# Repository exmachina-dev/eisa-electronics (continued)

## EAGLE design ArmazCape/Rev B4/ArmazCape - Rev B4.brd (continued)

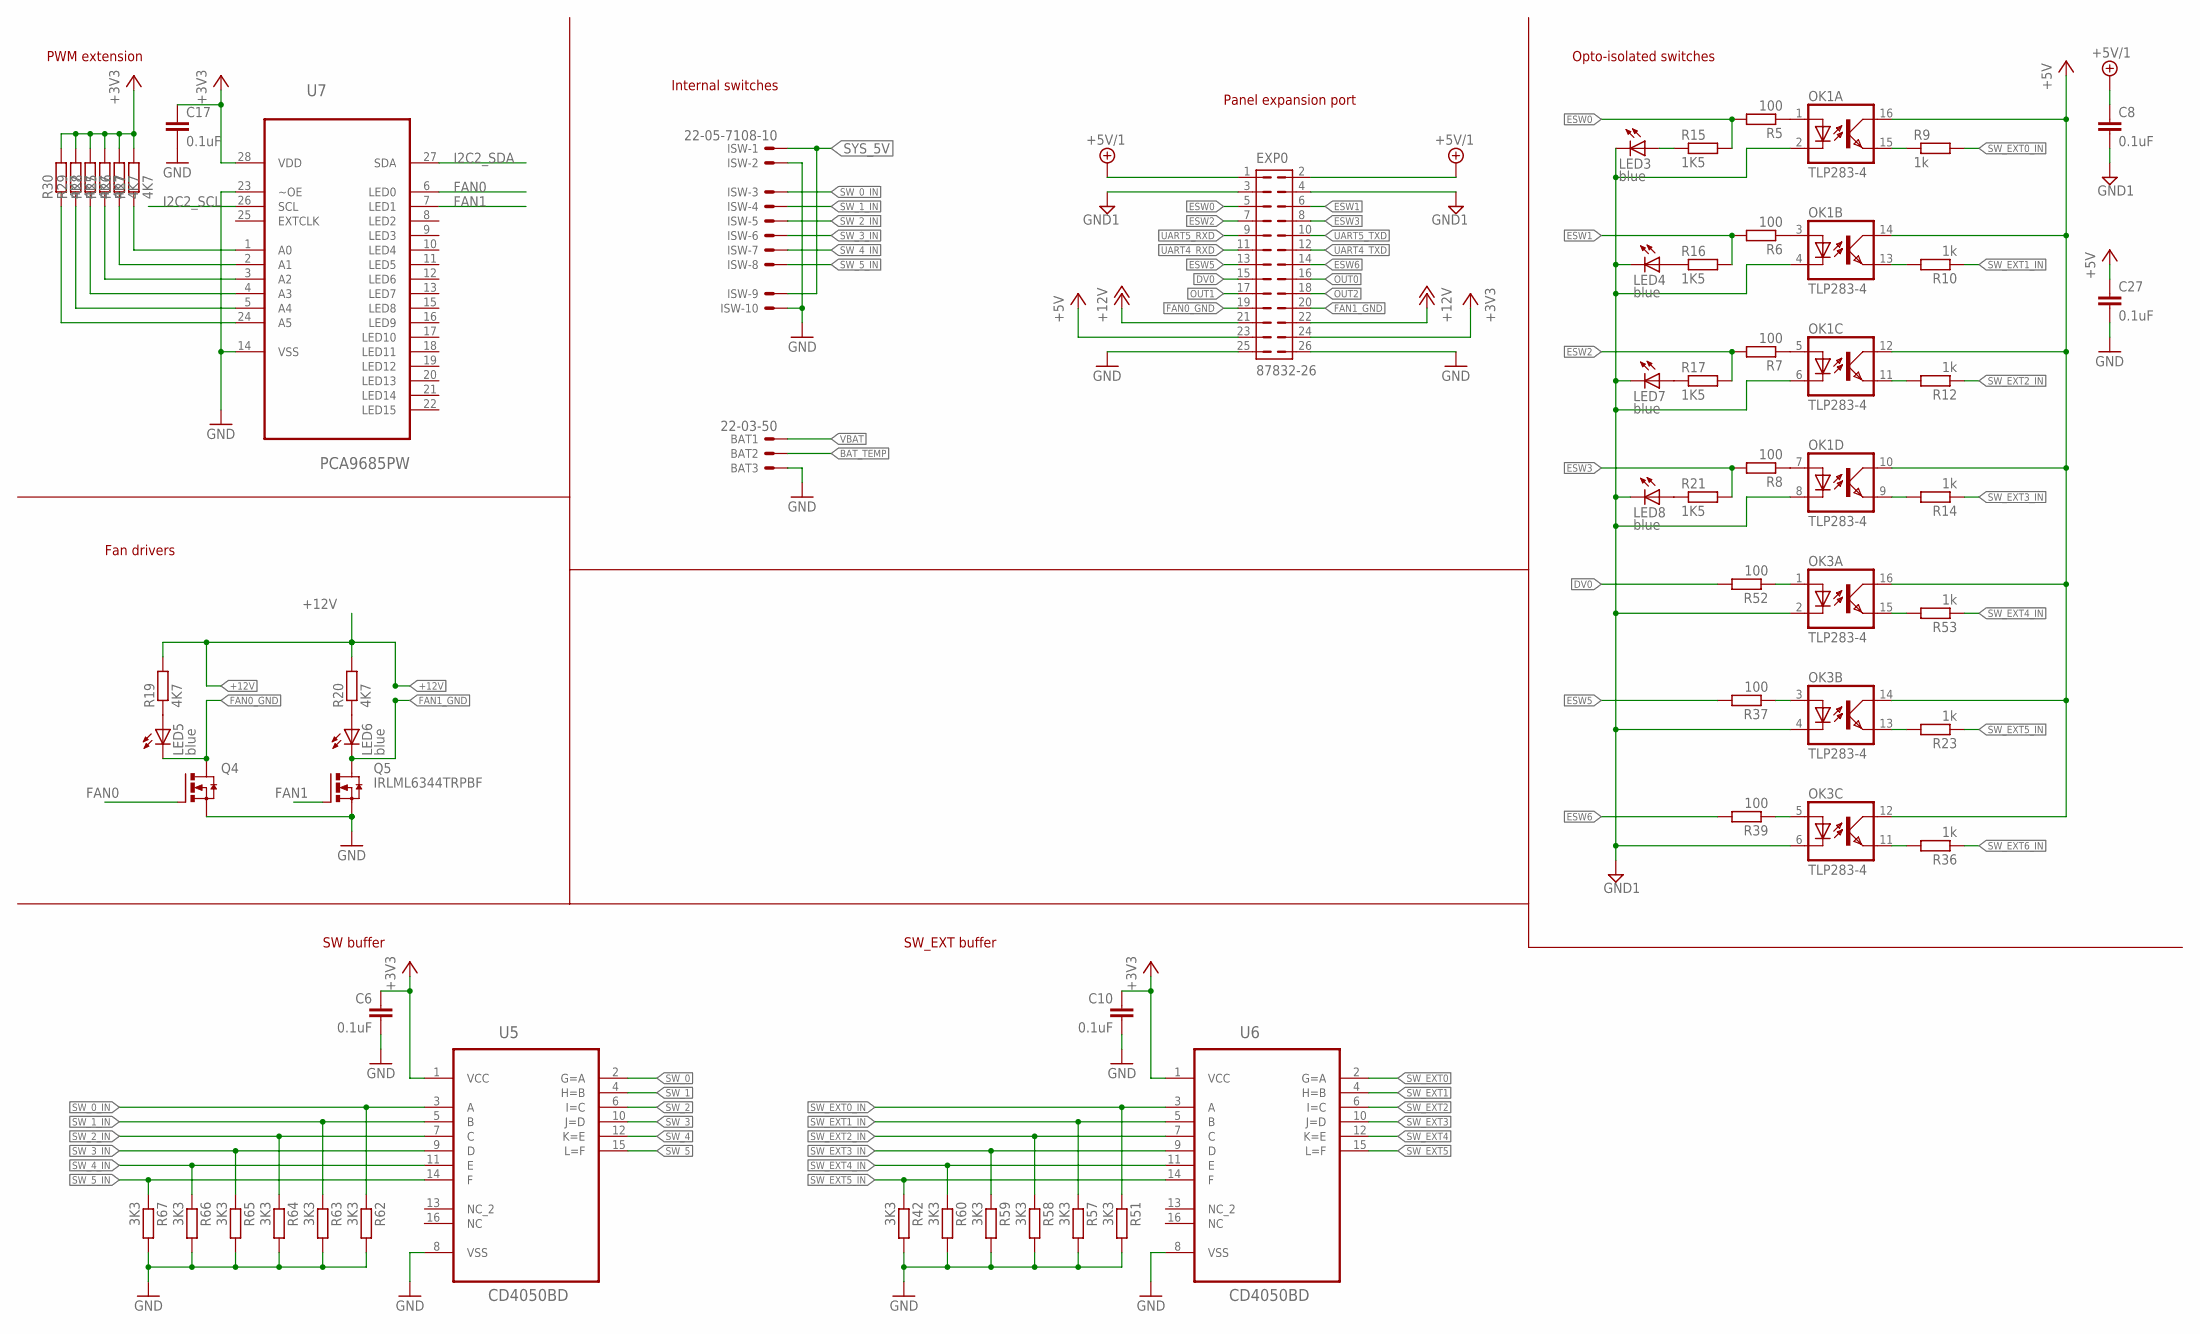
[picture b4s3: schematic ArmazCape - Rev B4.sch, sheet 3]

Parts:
BAT: 22-03-50; 5267-03A; MPN 22-03-5035
C6, C8, C10, C17, C27: 0.1uF; C0603; MPN GRM188R71H104KA93D
EXP0: 87832-26; MPN 87832-2620
ISW: 22-05-7108-10; 7395-10; MPN 22-05-7108
LED3, LED4, LED5, LED6, LED7, LED8: blue; CHIP-LED0603; MPN OVS-0603
OK1, OK3: TLP283-4; MINI-FLAT-16; MPN TCMT4100
Q4, Q5: IRLML6344TRPBF; SOT95P240X112-3N
R5, R6, R7, R8, R37, R39, R52: 100; R0603; MPN RC0603FR-07100RL
R9, R10, R12, R14, R23, R36, R53: 1k; R0603; MPN RC0603FR-071KL
R15, R16, R17, R21: 1K5; R0603; MPN RC0603FR-071K5L
R19, R20, R25, R26, R27, R28, R29, R30: 4K7; R0603; MPN RC0603FR-074K7L
R42, R51, R57, R58, R59, R60, R62, R63, R64, R65, R66, R67: 3K3; R0603; MPN RC0603FR-073K3L
U5, U6: CD4050BD; SOIC127P600X175-16N
U7: PCA9685PW; SOP65P640X110-28N

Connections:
+3V3: C6.1, C10.1, C17.1, EXP0.24, R25.2, R26.2, R27.2, R28.2, R29.2, R30.2, U5.1 (VCC), U6.1 (VCC), U7.28 (VDD); also elsewhere on the board
+5V: C27.1, EXP0.23, OK1.10 (COL), OK1.12 (COL), OK1.14 (COL), OK1.16 (COL), OK3.12 (COL), OK3.14 (COL), OK3.16 (COL); also elsewhere on the board
+5V/1: C8.1, EXP0.1, EXP0.2; also elsewhere on the board
+12V: EXP0.21, EXP0.22, R19.2, R20.2; also elsewhere on the board
BAT_TEMP: BAT.P2; also elsewhere on the board
DV0: EXP0.15, R52.2; also elsewhere on the board
ESW0: EXP0.5, R5.2, R15.2
ESW1: EXP0.6, R6.2, R16.2
ESW2: EXP0.7, R7.2, R17.2
ESW3: EXP0.8, R8.2, R21.2
ESW5: EXP0.13, R37.2
ESW6: EXP0.14, R39.2
FAN0: Q4.1 (G), U7.6 (LED0)
FAN0_GND: EXP0.19, LED5.C, Q4.3 (D)
FAN1: Q5.1 (G), U7.7 (LED1)
FAN1_GND: EXP0.20, LED6.C, Q5.3 (D)
GND: BAT.P3, C6.2, C10.2, C17.2, C27.2, EXP0.25, EXP0.26, ISW.2, ISW.10, Q4.2 (S), Q5.2 (S), R42.2, R51.2, R57.2, R58.2, R59.2, R60.2, R62.2, R63.2, R64.2, R65.2, R66.2, R67.2, U5.8 (VSS), U6.8 (VSS), U7.14 (VSS), U7.23 (~OE); also elsewhere on the board
GND1: C8.2, EXP0.3, EXP0.4, LED3.C, LED4.C, LED7.C, LED8.C, OK1.2 (C), OK1.4 (C), OK1.6 (C), OK1.8 (C), OK3.2 (C), OK3.4 (C), OK3.6 (C); also elsewhere on the board
I2C2_SCL: U7.26 (SCL); also elsewhere on the board
I2C2_SDA: U7.27 (SDA); also elsewhere on the board
unnamed: OK3.11 (EMIT), R36.2
unnamed: OK3.13 (EMIT), R23.2
unnamed: OK3.3 (A), R37.1
unnamed: LED5.A, R19.1
unnamed: OK1.1 (A), R5.1
unnamed: OK1.15 (EMIT), R9.1
unnamed: OK1.7 (A), R8.1
unnamed: OK1.9 (EMIT), R14.2
unnamed: OK1.11 (EMIT), R12.2
unnamed: OK1.13 (EMIT), R10.2
unnamed: LED3.A, R15.1
unnamed: OK1.3 (A), R6.1
unnamed: LED4.A, R16.1
unnamed: LED7.A, R17.1
unnamed: LED8.A, R21.1
unnamed: OK1.5 (A), R7.1
unnamed: OK3.5 (A), R39.1
unnamed: OK3.1 (A), R52.1
unnamed: OK3.15 (EMIT), R53.2
unnamed: R27.1, U7.1 (A0)
unnamed: R26.1, U7.2 (A1)
unnamed: R25.1, U7.3 (A2)
unnamed: R28.1, U7.4 (A3)
unnamed: R29.1, U7.5 (A4)
unnamed: R30.1, U7.24 (A5)
unnamed: LED6.A, R20.1
OUT0: EXP0.16; also elsewhere on the board
OUT1: EXP0.17; also elsewhere on the board
OUT2: EXP0.18; also elsewhere on the board
SW_0: U5.2 (G=A); also elsewhere on the board
SW_0_IN: ISW.3, R62.1, U5.3 (A)
SW_1: U5.4 (H=B); also elsewhere on the board
SW_1_IN: ISW.4, R63.1, U5.5 (B)
SW_2: U5.6 (I=C); also elsewhere on the board
SW_2_IN: ISW.5, R64.1, U5.7 (C)
SW_3: U5.10 (J=D); also elsewhere on the board
SW_3_IN: ISW.6, R65.1, U5.9 (D)
SW_4: U5.12 (K=E)
SW_4_IN: ISW.7, R66.1, U5.11 (E)
SW_5: U5.15 (L=F)
SW_5_IN: ISW.8, R67.1, U5.14 (F)
SW_EXT0: U6.2 (G=A); also elsewhere on the board
SW_EXT0_IN: R9.2, R51.1, U6.3 (A)
SW_EXT1: U6.4 (H=B); also elsewhere on the board
SW_EXT1_IN: R10.1, R57.1, U6.5 (B)
SW_EXT2: U6.6 (I=C); also elsewhere on the board
SW_EXT2_IN: R12.1, R58.1, U6.7 (C)
SW_EXT3: U6.10 (J=D); also elsewhere on the board
SW_EXT3_IN: R14.1, R59.1, U6.9 (D)
SW_EXT4: U6.12 (K=E); also elsewhere on the board
SW_EXT4_IN: R53.1, R60.1, U6.11 (E)
SW_EXT5: U6.15 (L=F); also elsewhere on the board
SW_EXT5_IN: R23.1, R42.1, U6.14 (F)
SW_EXT6_IN: R36.1; also elsewhere on the board
SYS_5V: ISW.1, ISW.9; also elsewhere on the board
UART4_RXD: EXP0.11; also elsewhere on the board
UART4_TXD: EXP0.12; also elsewhere on the board
UART5_RXD: EXP0.9; also elsewhere on the board
UART5_TXD: EXP0.10; also elsewhere on the board
VBAT: BAT.P1; also elsewhere on the board

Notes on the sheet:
Internal switches
PWM extension
SW buffer
Opto-isolated switches
Panel expansion port
SW_EXT buffer
Fan drivers

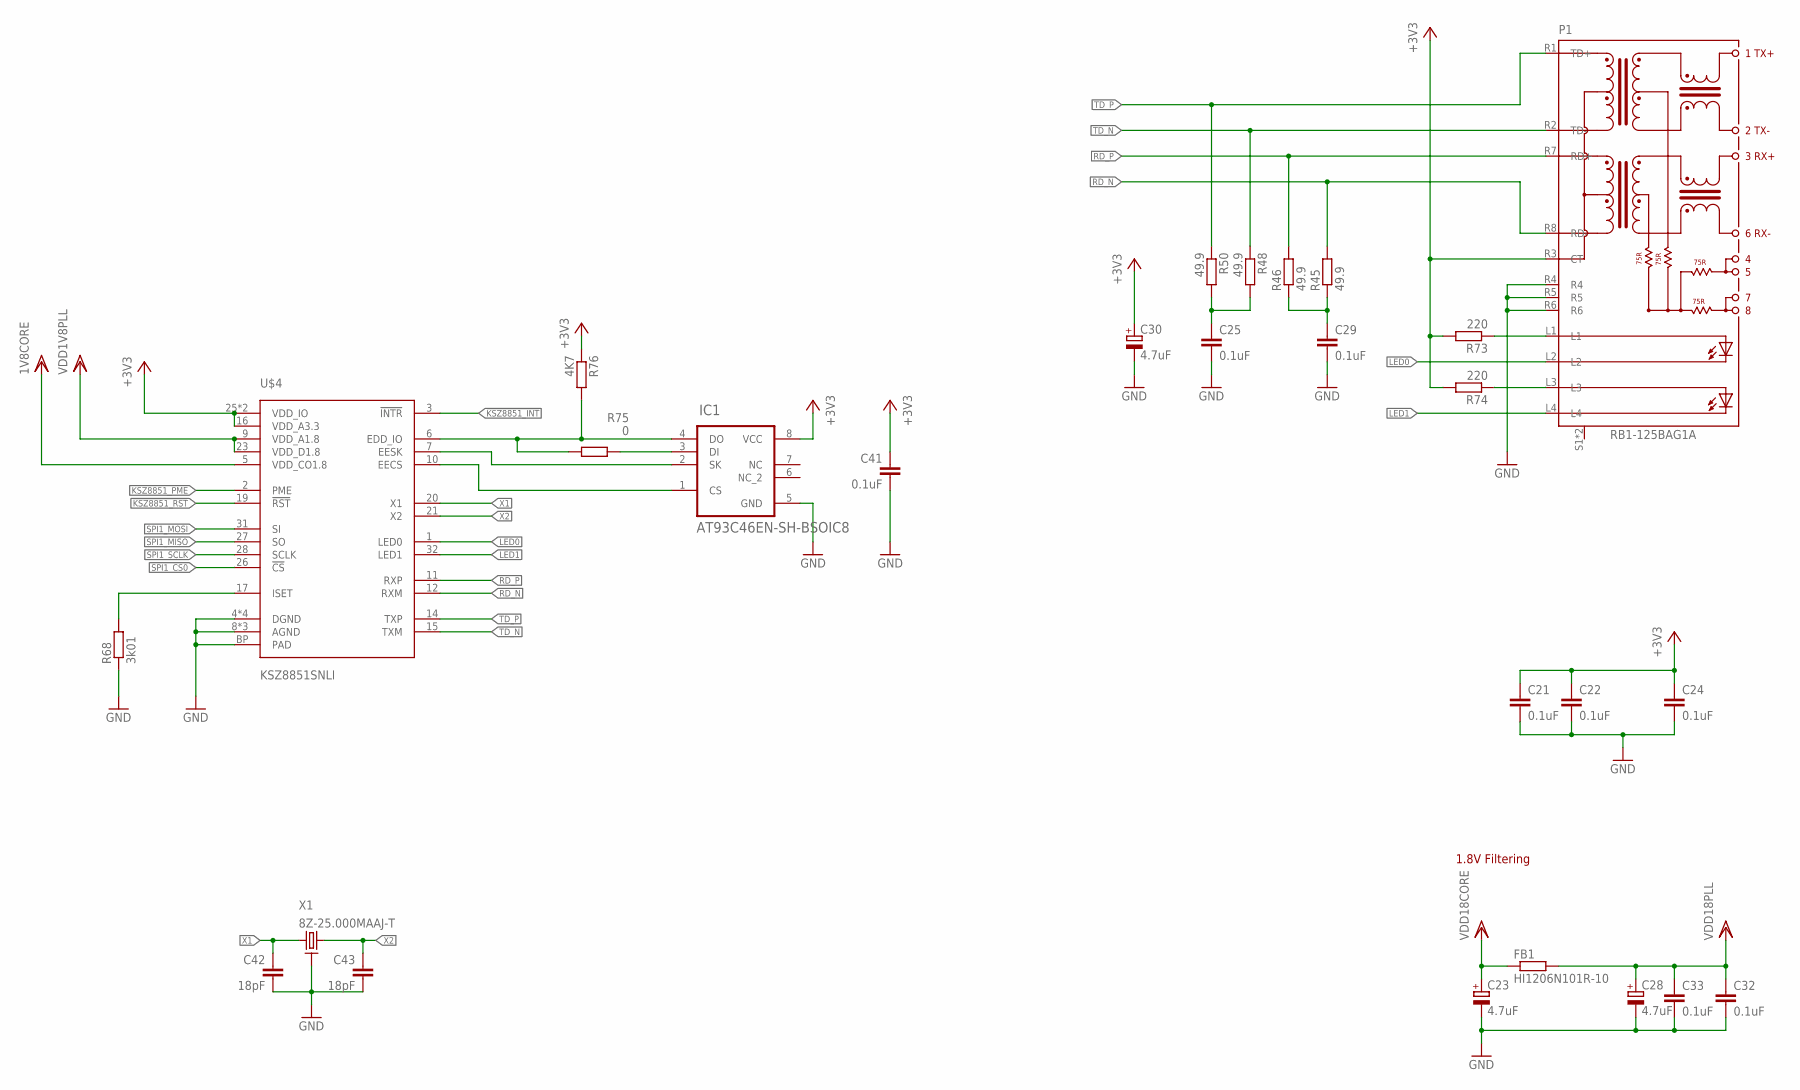
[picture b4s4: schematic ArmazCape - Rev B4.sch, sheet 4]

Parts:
C21, C22, C24, C25, C29, C32, C33, C41: 0.1uF; C0603; MPN GRM188R71H104KA93D
C23, C28, C30: 4.7uF; CT3216; MPN T491A475K010AT
C42, C43: 18pF; C0603; MPN MC0603N180J500CT
FB1: HI1206N101R-10; 1206
IC1: AT93C46EN-SH-BSOIC8; SOIC8; MPN AT93C46EN-SH-T
P1: RB1-125BAG1A; WIZNET_RB1-125BAG1A
R45, R46, R48, R50: 49.9; R0603; MPN RC0603FR-0749R9L
R68: 3k01; R0603; MPN MC0063W060313K01
R73, R74: 220; R0603; MPN MC0063W06031220R
R75: 0; R0603; MPN MC0603WG00000T5E-TC
R76: 4K7; R0603; MPN RC0603FR-074K7L
U$4: KSZ8851SNLI; QFN50P500X500X85-32L; MPN KSZ8851SNLI-TR
X1: 8Z-25.000MAAJ-T; SMD2.5X2; MPN 8Z-25.000MAAJ-T

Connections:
!KSZ8851_INT: U$4.3 (!INTR); also elsewhere on the board
!KSZ8851_RST: U$4.19 (!RST); also elsewhere on the board
+3V3: C21.1, C22.1, C24.1, C30.+, C41.1, IC1.8 (VCC), P1.R3 (CT), R73.2, R74.2, R76.1, U$4.16 (VDD_A3.3), U$4.25 (VDD_IO), U$4.30 (VDD_IO); also elsewhere on the board
EDDIO: IC1.4 (DO), R75.2, R76.2, U$4.6 (EDD_IO)
EECS: IC1.1 (CS), U$4.10 (EECS)
EESK: IC1.2 (SK), U$4.7 (EESK)
GND: C21.2, C22.2, C23.-, C24.2, C25.2, C28.-, C29.2, C30.-, C32.2, C33.2, C41.2, C42.2, C43.2, IC1.5 (GND), P1.R4, P1.R5, P1.R6, R68.1, U$4.4 (DGND), U$4.8 (AGND), U$4.13 (AGND), U$4.18 (AGND), U$4.22 (DGND), U$4.24 (DGND), U$4.29 (DGND), U$4.BP (PAD), X1.2, X1.4 (2); also elsewhere on the board
KSZ8851_PME: U$4.2 (PME)
LED0: P1.L2, U$4.1 (LED0)
LED1: P1.L4, U$4.32 (LED1)
unnamed: C25.1, R48.2, R50.2
unnamed: C29.1, R45.1, R46.1
unnamed: R68.2, U$4.17 (ISET)
unnamed: P1.L1, R73.1
unnamed: P1.L3, R74.1
unnamed: IC1.3 (DI), R75.1
RD_N: P1.R8 (RD-), R45.2, U$4.12 (RXM)
RD_P: P1.R7 (RD+), R46.2, U$4.11 (RXP)
SPI1_CS0: U$4.26 (!CS); also elsewhere on the board
SPI1_MISO: U$4.27 (SO); also elsewhere on the board
SPI1_MOSI: U$4.31 (SI); also elsewhere on the board
SPI1_SCLK: U$4.28 (SCLK); also elsewhere on the board
TD_N: P1.R2 (TD-), R48.1, U$4.15 (TXM)
TD_P: P1.R1 (TD+), R50.1, U$4.14 (TXP)
VDD18CORE: C23.+, FB1.1, U$4.5 (VDD_CO1.8)
VDD18PLL: C28.+, C32.1, C33.1, FB1.2, U$4.9 (VDD_A1.8), U$4.23 (VDD_D1.8)
X1: C42.1, U$4.20 (X1), X1.1
X2: C43.1, U$4.21 (X2), X1.3

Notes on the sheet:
1.8V Filtering

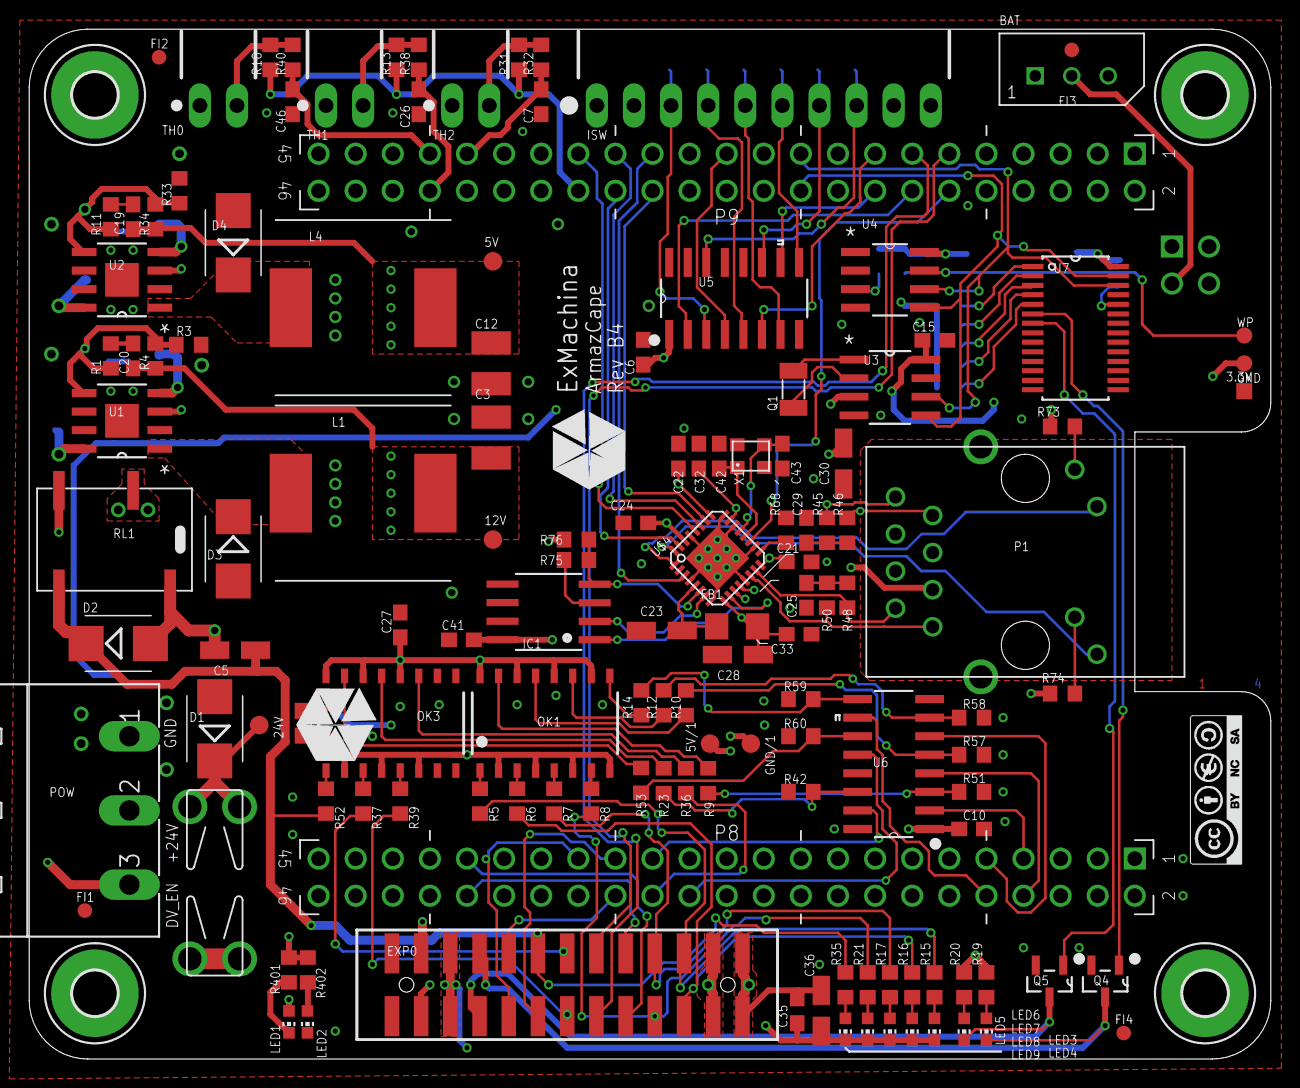
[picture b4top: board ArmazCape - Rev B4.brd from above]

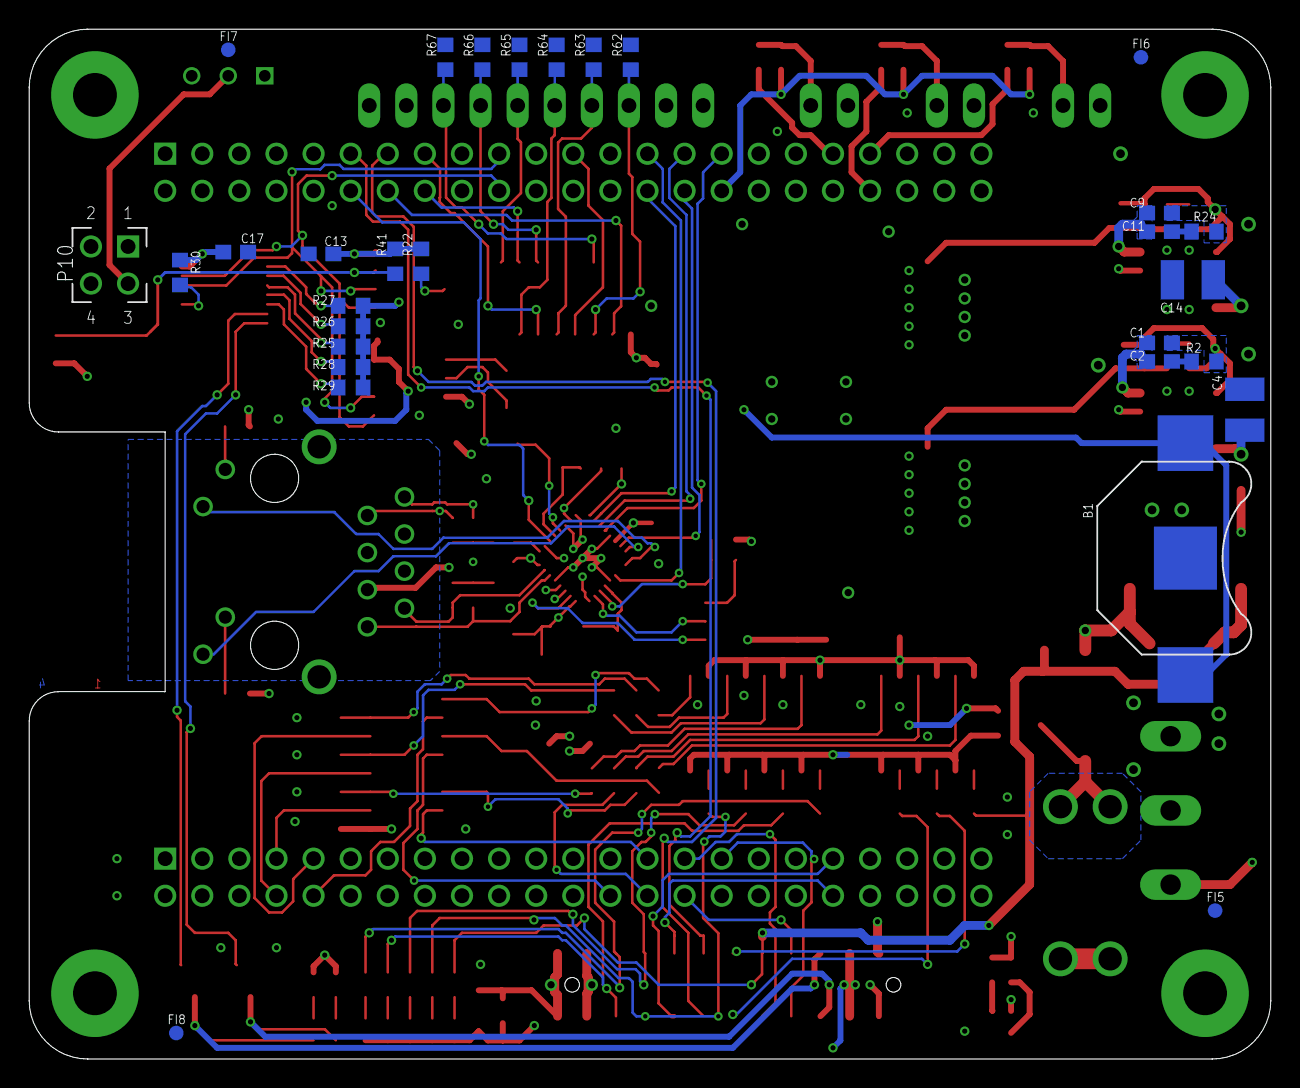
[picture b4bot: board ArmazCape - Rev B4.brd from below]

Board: 4 copper layers, 85.0 x 70.5 mm, 169 parts (29 on the bottom side), 131 nets.

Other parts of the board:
U$3: A4L-LOC
U$5: EXM-LOGO-BIG

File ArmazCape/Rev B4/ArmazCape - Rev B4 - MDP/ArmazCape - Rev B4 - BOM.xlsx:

Qty | Designator | Value | Package | Manufacteur | Reference Manufacteur | Mounting Tecghnologie | TO ODER | ORDER
1 | B1 | 3000 | 3000 | KEYSTONE | 3000 | SMD | Y | F
1 | BAT | 22-03-50 | 5267-03A | MOLEX | 22-03-5035 | Thought-Hole | N
1 | BB1 | BBB | BBB |  |  | Thought-Hole | N
1 | C1 | 470pF | C0603 | MURATA | GRM1885C1H471JA01D | SMD | Y | F
1 | C19 | 5.6nF | C0603 | KEMET | C0603C562J5GACTU | SMD | N
2 | C2, C11 | 22nF | C0603 | MURATA | GRM188R71H223KA01D | SMD | N
1 | C20 | 4.7nF | C0603 | MURATA | GRM188R71H472KA01D | SMD | N
2 | C3, C12 | 47uF, 16V | C1210 | MURATA | GRM32ER61C476KE15L | SMD | Y | F
2 | C4, C14 | 4.7uF, 50V | C1210 | AVX | 12105C475KAT2A | SMD | Y | F
2 | C42, C43 | 18pF | C0603 | MULTICOMP | MC0603N180J500CT | SMD | N
5 | C5, C23, C28, C30, C36 | 4.7uF | CT3216 | KEMET | T491A475K010AT | SMD | N
16 | C6, C8, C10, C13, C15, C17, C21, C22, C24, C25, C27, C29, C32, C33, C35, C41 | 0.1uF | C0603 | MURATA | GRM188R71H104KA93D | SMD | N
3 | C7, C26, C46 | 4.7uF | C0603 | MURATA | GRM188R60J475KE19D | SMD | N
1 | C9 | 330pF | C0603 | MURATA | GRM1885C1H331JA01D | SMD | Y | F
4 | D1, D2, D3, D4 | STPS3L40UF | SMB | STMICROELECTRONICS | STPS3L40UF | SMD | Y | F
1 | EXP0 | 87832-26 | 87832-26 | MOLEX | 87832-2620 | Thought-Hole | N
1 | FB1 | HI1206N101R-10 | 1206 | LAIRD TECHNOLOGIES | HI1206N101R-10 | SMD | N
1 | FU1 | 3557L | 3557-LITTLE | KEYSTONE | 3557 | Thought-Hole | N
1 | IC1 | AT93C46EN-SH-T | SOIC8 | MICROCHIP | AT93C46EN-SH-T | SMD | Y | F
1 | ISW | 22-05-7108-10 | 7395-10 | MOLEX | 22-05-7108 | Thought-Hole | N
1 | L1 | 47uH | WE-PD_1260/1245/1280/1210 | WURTH ELEKTRONIK | 7447709470 | SMD | N
1 | L4 | 33uH | WE-PD_1260/1245/1280/1210 | WURTH ELEKTRONIK | 7447709330 | SMD | Y | F
1 | LED1 | red | CHIP-LED0603 | MULTICOMP | OVS-0608 | SMD | Y | F
8 | LED2, LED3, LED4, LED5, LED6, LED7, LED8, LED9 | blue | CHIP-LED0603 | MULTICOMP | OVS-0603 | SMD | Y | F
2 | OK1, OK3 | TLP283-4 | MINI-FLAT-16 | VISHAY/TELEFUNKEN | TCMT4100 | SMD | Y | F
1 | P1 | RB1-125BAG1A | WIZNET_RB1-125BAG1A | WIZNET | RB1-125BAG1A | SMD | N
1 | POW | MSTBA3 | MSTBA3 | PHOENIX | 1757255 | Thought-Hole | N
1 | Q1 | 32.768kHz, 12.5pF | ABS07 | ABRACON | ABS06-32.768KHZ-T | SMD | N
2 | Q4, Q5 | IRLML6344TRPBF | SOT95P240X112-3N | INTERNATIONAL RECTIFIER | IRLML6344TRPBF | SMD | Y | F
1 | R1 | 200 | R0603 | YAGEO | RC0603FR-07200RL | SMD | Y | M
1 | R11 | 160 | R0603 | YAGEO | RC0603FR-07160RL | SMD | N
16 | R13, R18, R19, R20, R22, R25, R26, R27, R28, R29, R30, R31, R41, R76, R401, R402 | 4K7 | R0603 | YAGEO | RC0603FR-074K7L | SMD | N
5 | R15, R16, R17, R21, R35 | 1K5 | R0603 | YAGEO | RC0603FR-071K5L | SMD | Y | F
1 | R2 | 2K2 | R0603 | YAGEO | RC0603FR-072K2L | SMD | N
1 | R24 | 3K6 | R0603 | YAGEO | RC0603FR-073K6L | SMD | N
1 | R3 | 270 | R0603 | YAGEO | RC0603FR-07270RL | SMD | N
3 | R32, R38, R40 | 10K | R0603 | YAGEO | RC0603FR-0710KL | SMD | N
1 | R33 | 698 | R0603 | YAGEO | RC0603FR-07698RL | SMD | N
2 | R4, R34 | 5K1 | R0603 | YAGEO | RC0603FR-075K1L | SMD | N
12 | R42, R51, R57, R58, R59, R60, R62, R63, R64, R65, R66, R67 | 3K3 | R0603 | YAGEO | RC0603FR-073K3L | SMD | N
4 | R45, R46, R48, R50 | 49.9 | R0603 | YAGEO | RC0603FR-0749R9L | SMD | N
7 | R5, R6, R7, R8, R37, R39, R52 | 100 | R0603 | YAGEO | RC0603FR-07100RL | SMD | N
1 | R68 | 3k01 | R0603 | MULTICOMP | MC0063W060313K01 | SMD | Y | F
2 | R73, R74 | 220 | R0603 | MULTICOMP | MCWR06X2200FTL | SMD | Y | F
1 | R75 | 0 | R0603 | MULTICOMP | MC0603WG00000T5E-TC | SMD | N
7 | R9, R10, R12, R14, R23, R36, R53 | 1k | R0603 | YAGEO | RC0603FR-071KL | SMD | N
1 | RL1 | G6L-1F DC5 | G6L-1F | OMRON COMPONENTS USA | G6L-1F DC5 | SMD | Y | M
3 | TH0, TH1, TH2 | 22-05-7028-02 | 7395-02 | MOLEX | 22-05-7028 | Thought-Hole | N
1 | U$4 | KSZ8851SNLI | QFN50P500X500X85-32L | MICROCHIP | KSZ8851SNLI-TR | SMD | Y | F
2 | U1, U2 | L7985A | SOIC127P600X170-9N | STMICROELECTRONICS | L7985A | SMD | Y | M
1 | U3 | DS1307ZN+ | MAXIM_SOIC127P600X175-8N | Maxim | DS1307ZN+ | SMD | Y | M
1 | U4 | 24AA256-I/SN | MICROCHIP_BY_ELEMENT14_BATCH_1_SOIC127P600X175-8N | MICROCHIP | 24AA256-I/SN | SMD | Y | F
2 | U5, U6 | CD4050BD | SOIC127P600X175-16N | Texas Instrument | CD4050BD | SMD | Y | F
1 | U7 | PCA9685PW | SOP65P640X110-28N | NXP | PCA9685PW | SMD | Y | F
1 | X1 | 8Z-25.000MAAJ-T | SMD2.5X2 | TXC | 8Z-25.000MAAJ-T | SMD | Y | F

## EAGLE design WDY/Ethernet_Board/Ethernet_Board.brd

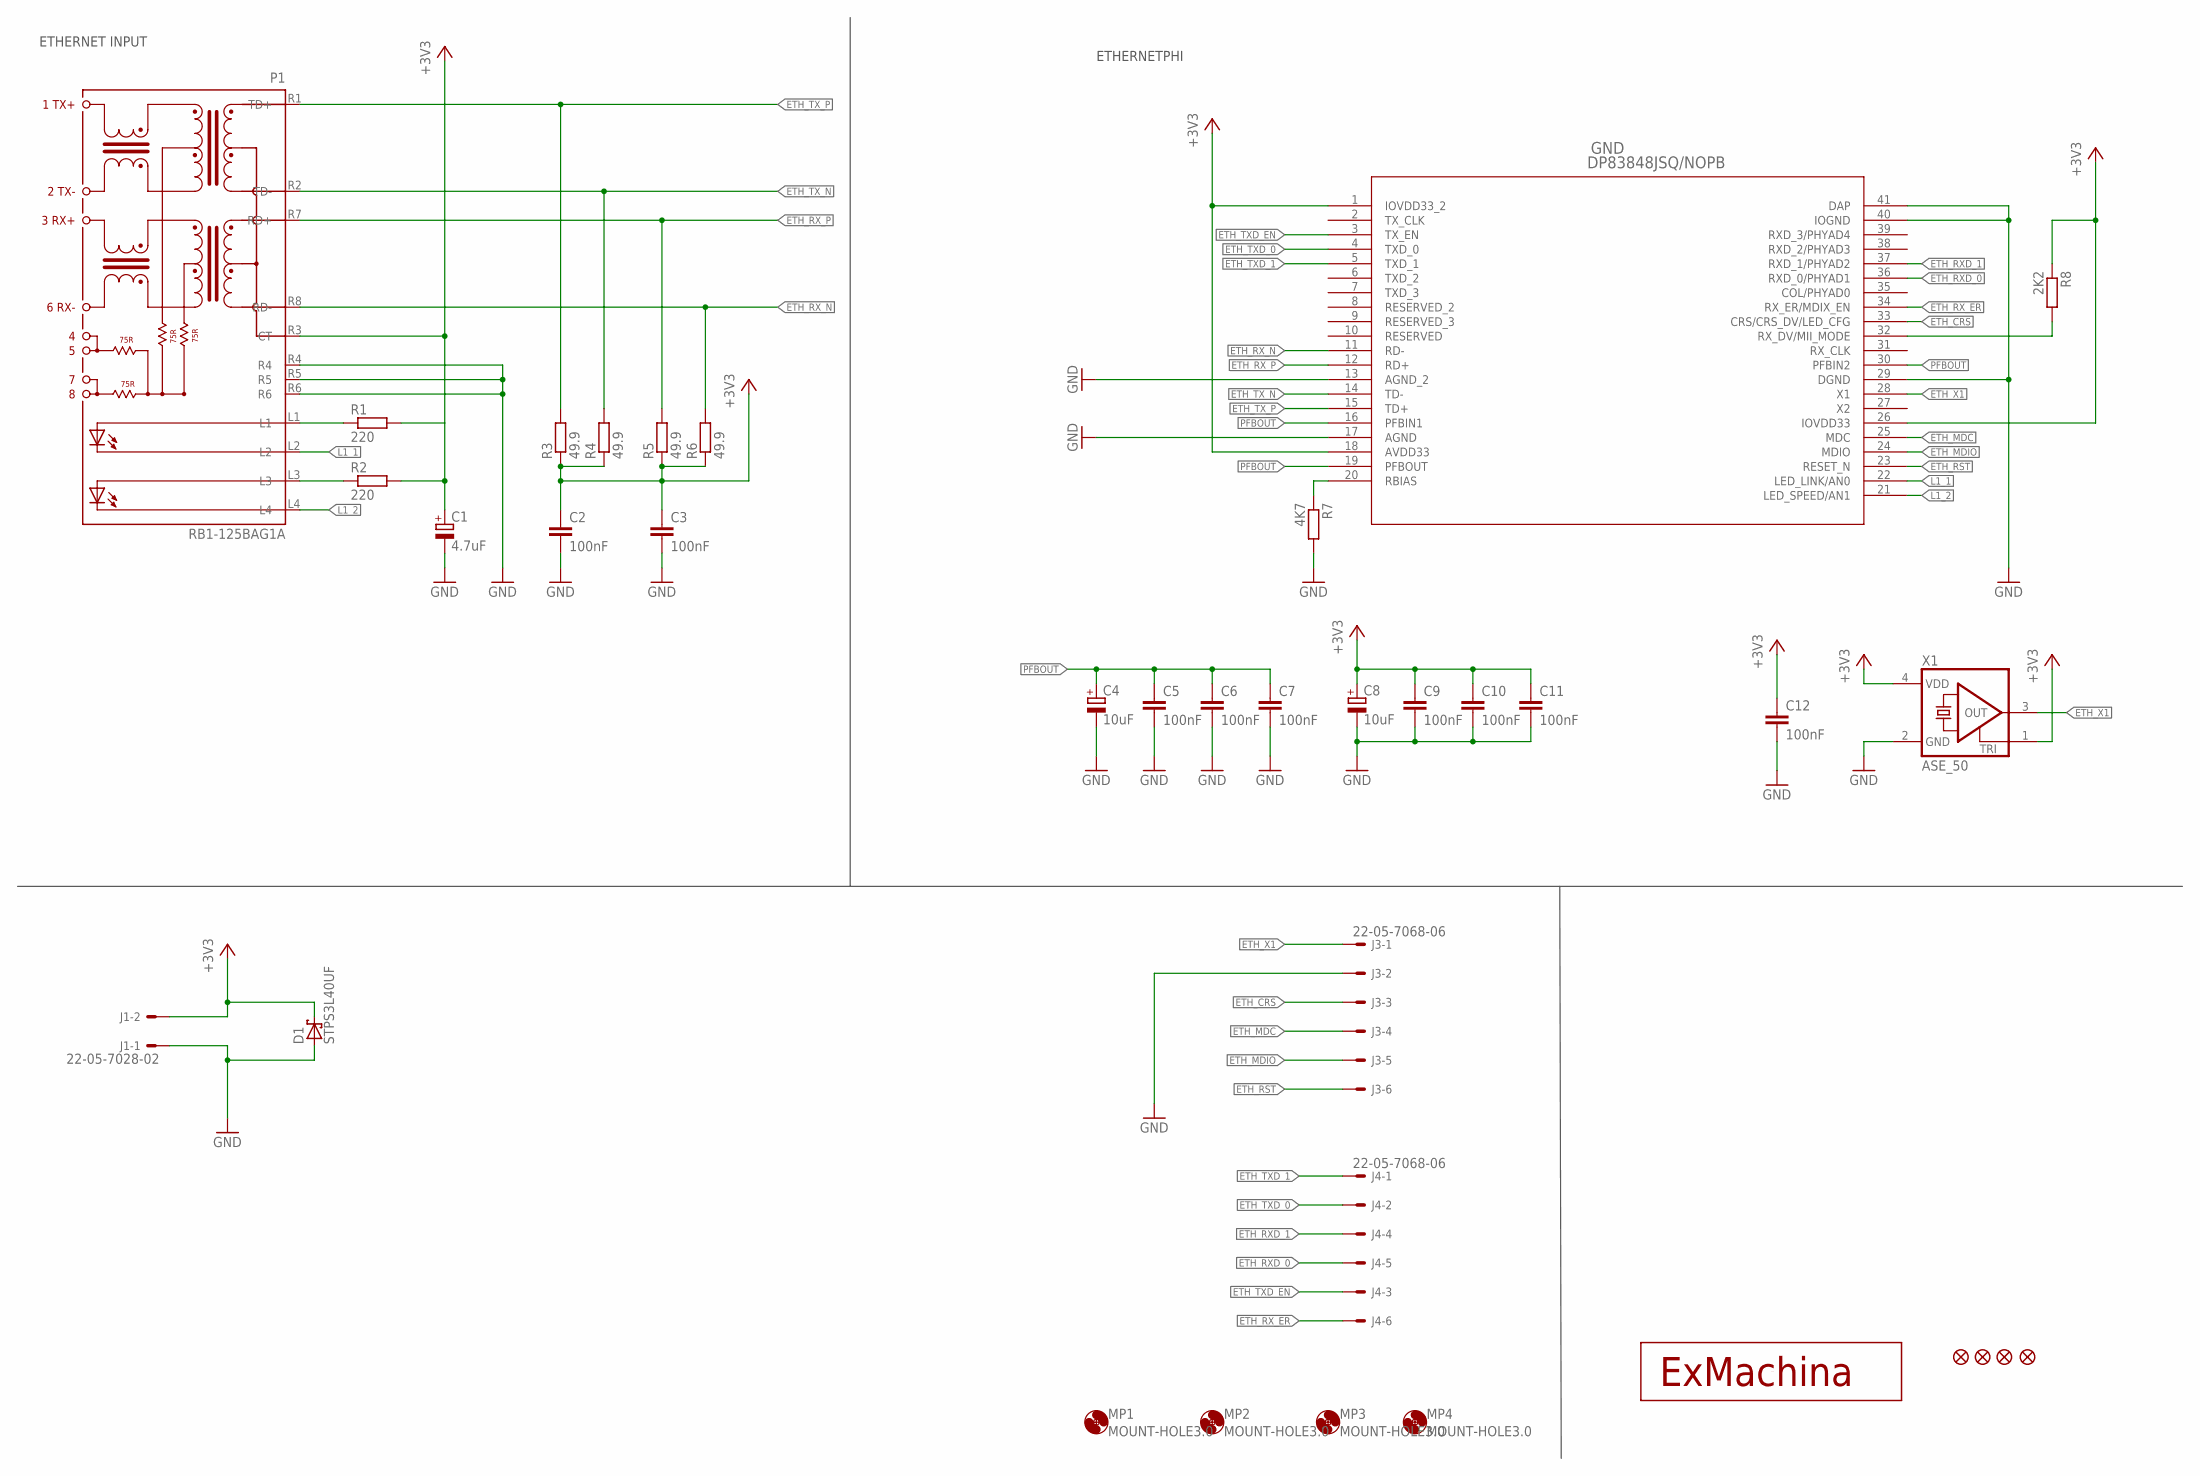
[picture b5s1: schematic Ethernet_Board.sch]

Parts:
C1: 4.7uF; CT3216
C2, C3, C5, C6, C7, C9, C10, C11, C12: 100nF; C0603
C4, C8: 10uF; CT3216
D1: STPS3L40UF; SMB
GND: DP83848JSQ/NOPB; SQA40B
J1: 22-05-7028-02; 7395-02
J3, J4: 22-05-7068-06; 7395-06
JP1, JP2, JP3, JP4: FIDUCIAL1X2; FIDUCIAL-1X2
MP1, MP2, MP3, MP4: MOUNT-HOLE3.0; 3,0
P1: RB1-125BAG1A; WIZNET_RB1-125BAG1A
R1, R2: 220; R0603
R3, R4, R5, R6: 49.9; R0603
R7: 4K7; R0603
R8: 2K2; R0603
T1: EXMACHINA-LOGO-NAME; EXM-LOGO-BASELINE
X1: ASE_50; ASE

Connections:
+3V3: C1.+, C2.1, C3.1, C8.+, C9.1, C10.1, C11.1, C12.1, D1.C, GND.1 (IOVDD33_2), GND.18 (AVDD33), GND.26 (IOVDD33), J1.2, P1.R3 (CT), R1.2, R2.2, R3.1, R4.1, R5.1, R6.1, R8.1, X1.1 (TRI), X1.4 (VDD)
ETH_CRS: GND.33 (CRS/CRS_DV/LED_CFG), J3.3
ETH_MDC: GND.25 (MDC), J3.4
ETH_MDIO: GND.24 (MDIO), J3.5
ETH_RST: GND.23 (RESET_N), J3.6
ETH_RXD_0: GND.36 (RXD_0/PHYAD1), J4.5
ETH_RXD_1: GND.37 (RXD_1/PHYAD2), J4.4
ETH_RX_ER: GND.34 (RX_ER/MDIX_EN), J4.6
ETH_RX_N: GND.11 (RD-), P1.R8 (RD-), R6.2
ETH_RX_P: GND.12 (RD+), P1.R7 (RD+), R5.2
ETH_TXD_0: GND.4 (TXD_0), J4.2
ETH_TXD_1: GND.5 (TXD_1), J4.1
ETH_TXD_EN: GND.3 (TX_EN), J4.3
ETH_TX_N: GND.14 (TD-), P1.R2 (TD-), R4.2
ETH_TX_P: GND.15 (TD+), P1.R1 (TD+), R3.2
ETH_X1: GND.28 (X1), J3.1, X1.3 (OUT)
GND: C1.-, C2.2, C3.2, C4.-, C5.2, C6.2, C7.2, C8.-, C9.2, C10.2, C11.2, C12.2, D1.A, GND.13 (AGND_2), GND.17 (AGND), GND.29 (DGND), GND.40 (IOGND), GND.41 (DAP), J1.1, J3.2, P1.R4, P1.R5, P1.R6, R7.2, X1.2 (GND)
L1_1: GND.22 (LED_LINK/AN0), P1.L2
L1_2: GND.21 (LED_SPEED/AN1), P1.L4
MII_MODE: GND.32 (RX_DV/MII_MODE), R8.2
unnamed: GND.20 (RBIAS), R7.1
unnamed: P1.L1, R1.1
unnamed: P1.L3, R2.1
PFBOUT: C4.+, C5.1, C6.1, C7.1, GND.16 (PFBIN1), GND.19 (PFBOUT), GND.30 (PFBIN2)

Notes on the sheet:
ETHERNET INPUT
ETHERNETPHI

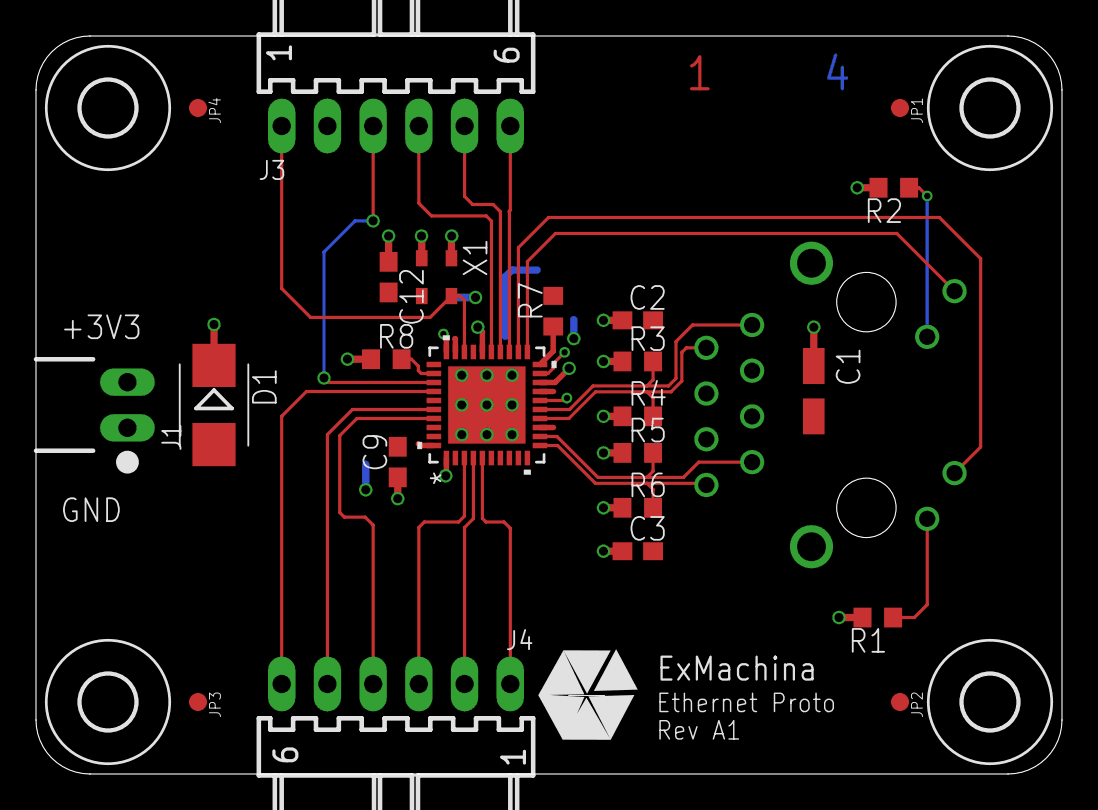
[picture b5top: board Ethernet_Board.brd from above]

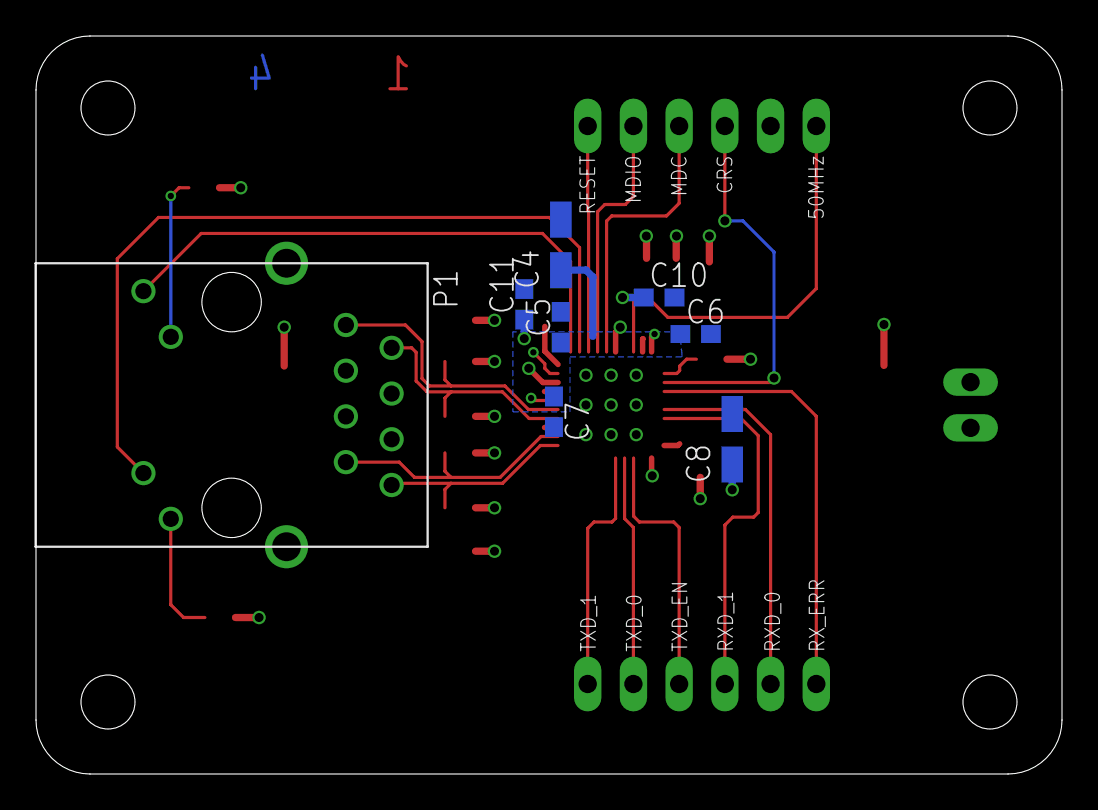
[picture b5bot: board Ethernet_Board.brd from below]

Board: 4 copper layers, 57.0 x 41.0 mm, 36 parts (8 on the bottom side), 24 nets.
